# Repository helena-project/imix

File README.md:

imix
====

This open source, feature packed board is an all-in-one development kit for ultra 
low power Internet-of-Things research and prototyping. With a Cortex M4 microcontroller,
BLE/ANT and 802.15.4 radio modules, sensing, battery charging, and tons of I/O,
imix has everything you need to prototype and profile your next big IoT
breakthrough. Pair imix with the [Tock](http://github.com/helena-project/tock)
operating system to quickly develop secure embedded applications.

Features:
- Codeveloped with [Tock](http://github.com/helena-project/tock), a next-generation secure embedded operating system
- ATMEL SAM4L low power microcontroller with a Cortex M4 core
- NRF51422 radio with a Cortex M0 core for communication over Bluetooth Low Energy or ANT
- AT86RF233 radio for communication over 802.15.4
- Low power 3-axis linear accelerometer + 3-axis magnetometer
- Temperature + humidity sensor
- Digital light sensor
- Serial-to-USB and native USB ports
- Auditable True Random Number Generator
- Individually turn each subsystem completely on or off
- Easily measure the power consumption of each subsystem
- Compatible with most Arduino shields
- Integrated lithium polymer battery charger, and optional battery clips for the standard 18650 size

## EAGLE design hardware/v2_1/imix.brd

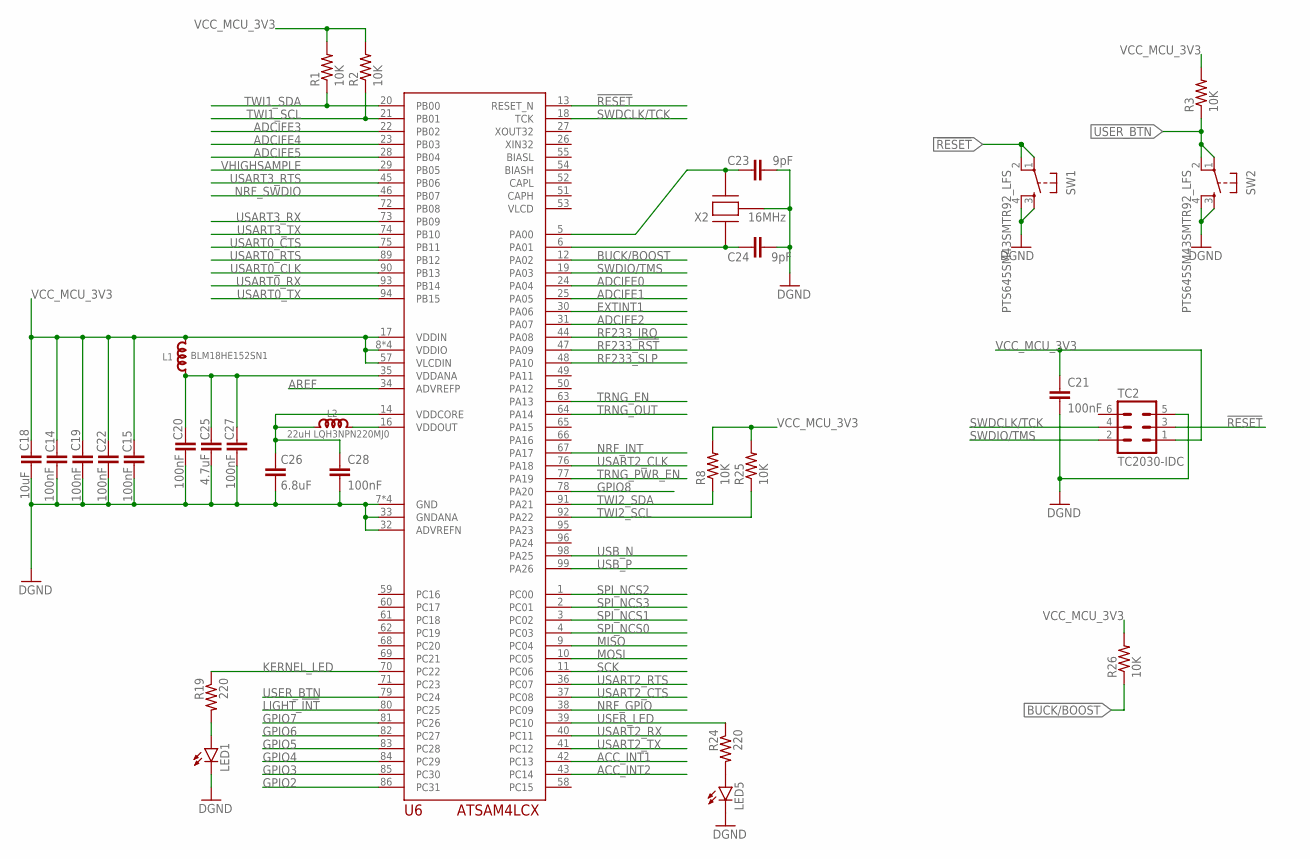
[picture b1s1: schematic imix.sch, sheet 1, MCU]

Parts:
C14, C15, C19, C20, C21, C22, C27, C28: 100nF; C0603
C18: 10uF; C0603
C23, C24: 9pF; C0603
C25: 4.7uF; C0603
C26: 6.8uF; C0603
L1: BLM18HE152SN1; L0603
L2: 22uH LQH3NPN220MJ0; L1212
LED1, LED5: LED-BLUE0603; LED-0603
R1, R2, R3, R8, R25, R26: 10K; 0603-RES
R19, R24: 220; 0603-RES
SW1, SW2: PTS645SM43SMTR92_LFS; TAC_SWITCH_6X6
TC2: TC2030-IDC
U6: ATSAM4LCX_100; TQFP100
X2: 16MHz; CTS_405_SERIES

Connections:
!RESET: SW1.1, SW1.2, TC2.3, U6.13 (RESET_N); also elsewhere on the board
ACC_INT1: U6.42 (PC13); also elsewhere on the board
ACC_INT2: U6.43 (PC14); also elsewhere on the board
ADCIFE0: U6.24 (PA04); also elsewhere on the board
ADCIFE1: U6.25 (PA05); also elsewhere on the board
ADCIFE2: U6.31 (PA07); also elsewhere on the board
ADCIFE3: U6.22 (PB02); also elsewhere on the board
ADCIFE4: U6.23 (PB03); also elsewhere on the board
ADCIFE5: U6.28 (PB04); also elsewhere on the board
AREF: U6.34 (ADVREFP); also elsewhere on the board
BIASH: U6.54 (BIASH)
BIASL: U6.55 (BIASL)
BUCK/BOOST: R26.1, U6.12 (PA02)
EXTINT1: U6.30 (PA06); also elsewhere on the board
GND: C14.1, C15.1, C18.1, C19.1, C20.2, C21.2, C22.1, C23.2, C24.2, C25.2, C26.2, C27.2, C28.2, LED1.C, LED5.C, SW1.3, SW1.4, SW2.3, SW2.4, TC2.5, U6.7 (GND), U6.15 (GND), U6.32 (ADVREFN), U6.33 (GNDANA), U6.56 (GND), U6.100 (GND), X2.CASE@2 (CASE), X2.CASE@4 (CASE); also elsewhere on the board
GPIO2: U6.86 (PC31); also elsewhere on the board
GPIO3: U6.85 (PC30); also elsewhere on the board
GPIO4: U6.84 (PC29); also elsewhere on the board
GPIO5: U6.83 (PC28); also elsewhere on the board
GPIO6: U6.82 (PC27); also elsewhere on the board
GPIO7: U6.81 (PC26); also elsewhere on the board
GPIO8: U6.78 (PA20); also elsewhere on the board
KERNEL_LED: R19.1, U6.70 (PC22)
LIGHT_!INT: U6.80 (PC25); also elsewhere on the board
MCU_VOUT3.3: L2.2, U6.16 (VDDOUT)
MISO: U6.9 (PC04); also elsewhere on the board
MOSI: U6.10 (PC05); also elsewhere on the board
unnamed: C20.1, C25.1, C27.1, L1.1, U6.35 (VDDANA)
unnamed: C24.1, U6.6 (PA01), X2.1
unnamed: C26.1, C28.1, L2.1, U6.14 (VDDCORE)
unnamed: C23.1, U6.5 (PA00), X2.3 (2)
unnamed: LED1.A, R19.2
unnamed: LED5.A, R24.2
NRF_GPIO: U6.38 (PC09); also elsewhere on the board
NRF_INT: U6.67 (PA17); also elsewhere on the board
NRF_SWDIO: U6.46 (PB07); also elsewhere on the board
RF233_!RST: U6.47 (PA09); also elsewhere on the board
RF233_IRQ: U6.44 (PA08); also elsewhere on the board
RF233_SLP: U6.48 (PA10); also elsewhere on the board
SCK: U6.11 (PC06); also elsewhere on the board
SPI_NCS0: U6.4 (PC03); also elsewhere on the board
SPI_NCS1: U6.3 (PC02); also elsewhere on the board
SPI_NCS2: U6.1 (PC00); also elsewhere on the board
SPI_NCS3: U6.2 (PC01); also elsewhere on the board
SWDCLK/TCK: TC2.4, U6.18 (TCK)
SWDIO/TMS: TC2.2, U6.19 (PA03)
TRNG_EN: U6.63 (PA13); also elsewhere on the board
TRNG_OUT: U6.64 (PA14); also elsewhere on the board
TRNG_PWR_EN: U6.77 (PA19); also elsewhere on the board
TWI1_SCL: R2.1, U6.21 (PB01); also elsewhere on the board
TWI1_SDA: R1.1, U6.20 (PB00); also elsewhere on the board
TWI2_SCL: R25.1, U6.92 (PA22); also elsewhere on the board
TWI2_SDA: R8.1, U6.91 (PA21); also elsewhere on the board
USART0_CLK: U6.90 (PB13); also elsewhere on the board
USART0_CTS: U6.75 (PB11); also elsewhere on the board
USART0_RTS: U6.89 (PB12); also elsewhere on the board
USART0_RX: U6.93 (PB14); also elsewhere on the board
USART0_TX: U6.94 (PB15); also elsewhere on the board
USART2_CLK: U6.76 (PA18); also elsewhere on the board
USART2_CTS: U6.37 (PC08); also elsewhere on the board
USART2_RTS: U6.36 (PC07); also elsewhere on the board
USART2_RX: U6.40 (PC11); also elsewhere on the board
USART2_TX: U6.41 (PC12); also elsewhere on the board
USART3_RTS: U6.45 (PB06); also elsewhere on the board
USART3_RX: U6.73 (PB09); also elsewhere on the board
USART3_TX: U6.74 (PB10); also elsewhere on the board
USB_N: U6.98 (PA25); also elsewhere on the board
USB_P: U6.99 (PA26); also elsewhere on the board
USER_BTN: R3.1, SW2.1, SW2.2, U6.79 (PC24); also elsewhere on the board
USER_LED: R24.1, U6.39 (PC10)
VCC_MCU_3V3: C14.2, C15.2, C18.2, C19.2, C21.1, C22.2, L1.2, R1.2, R2.2, R3.2, R8.2, R25.2, R26.2, TC2.1, U6.8 (VDDIO), U6.17 (VDDIN), U6.57 (VLCDIN), U6.87 (VDDIO), U6.88 (VDDIO), U6.97 (VDDIO); also elsewhere on the board
VHIGHSAMPLE: U6.29 (PB05); also elsewhere on the board

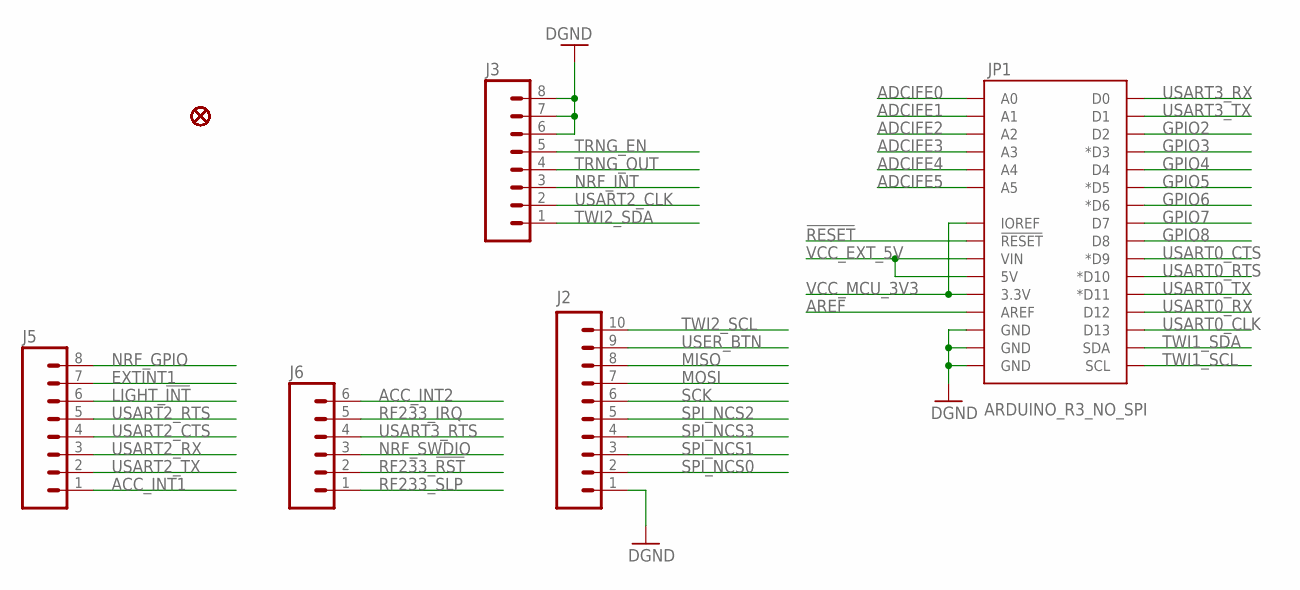
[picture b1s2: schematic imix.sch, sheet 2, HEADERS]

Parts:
J2: M10NO_SILK_PTH_FEMALE; 1X10_NO_SILK
J3, J5: M08NO_SILK_FEMALE_PTH; 1X08_NO_SILK
J6: M06NO_SILK_FEMALE_PTH; 1X06_NO_SILK
JP1: ARDUINO_R3_NO_SPI; ARDUINO_R3_NO_HOLES_NO_SPI
U$2, U$3, U$5, U$6, U$7, U$8, U$10, U$11, U$12, U$13, U$14, U$15, U$16, U$17, U$18: FIDUCIAL

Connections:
!RESET: JP1.RESET@1 (!RESET!); also elsewhere on the board
ACC_INT1: J5.1; also elsewhere on the board
ACC_INT2: J6.6; also elsewhere on the board
ADCIFE0: JP1.A0; also elsewhere on the board
ADCIFE1: JP1.A1; also elsewhere on the board
ADCIFE2: JP1.A2; also elsewhere on the board
ADCIFE3: JP1.A3; also elsewhere on the board
ADCIFE4: JP1.A4; also elsewhere on the board
ADCIFE5: JP1.A5; also elsewhere on the board
AREF: JP1.AREF; also elsewhere on the board
EXTINT1: J5.7; also elsewhere on the board
GND: J2.1, J3.6, J3.7, J3.8, JP1.GND@1 (GND), JP1.GND@2 (GND), JP1.GND@3 (GND); also elsewhere on the board
GPIO2: JP1.D2; also elsewhere on the board
GPIO3: JP1.D3 (*D3); also elsewhere on the board
GPIO4: JP1.D4; also elsewhere on the board
GPIO5: JP1.D5 (*D5); also elsewhere on the board
GPIO6: JP1.D6 (*D6); also elsewhere on the board
GPIO7: JP1.D7; also elsewhere on the board
GPIO8: JP1.D8; also elsewhere on the board
LIGHT_!INT: J5.6; also elsewhere on the board
MISO: J2.8; also elsewhere on the board
MOSI: J2.7; also elsewhere on the board
NRF_GPIO: J5.8; also elsewhere on the board
NRF_INT: J3.3; also elsewhere on the board
NRF_SWDIO: J6.3; also elsewhere on the board
RF233_!RST: J6.2; also elsewhere on the board
RF233_IRQ: J6.5; also elsewhere on the board
RF233_SLP: J6.1; also elsewhere on the board
SCK: J2.6; also elsewhere on the board
SPI_NCS0: J2.2; also elsewhere on the board
SPI_NCS1: J2.3; also elsewhere on the board
SPI_NCS2: J2.5; also elsewhere on the board
SPI_NCS3: J2.4; also elsewhere on the board
TRNG_EN: J3.5; also elsewhere on the board
TRNG_OUT: J3.4; also elsewhere on the board
TWI1_SCL: JP1.SCL; also elsewhere on the board
TWI1_SDA: JP1.SDA; also elsewhere on the board
TWI2_SCL: J2.10; also elsewhere on the board
TWI2_SDA: J3.1; also elsewhere on the board
USART0_CLK: JP1.D13; also elsewhere on the board
USART0_CTS: JP1.D9 (*D9); also elsewhere on the board
USART0_RTS: JP1.D10 (*D10); also elsewhere on the board
USART0_RX: JP1.D12; also elsewhere on the board
USART0_TX: JP1.D11 (*D11); also elsewhere on the board
USART2_CLK: J3.2; also elsewhere on the board
USART2_CTS: J5.4; also elsewhere on the board
USART2_RTS: J5.5; also elsewhere on the board
USART2_RX: J5.3; also elsewhere on the board
USART2_TX: J5.2; also elsewhere on the board
USART3_RTS: J6.4; also elsewhere on the board
USART3_RX: JP1.D0; also elsewhere on the board
USART3_TX: JP1.D1; also elsewhere on the board
USER_BTN: J2.9; also elsewhere on the board
VCC_EXT_5V: JP1.5V, JP1.VIN; also elsewhere on the board
VCC_MCU_3V3: JP1.3.3V, JP1.IOREF; also elsewhere on the board

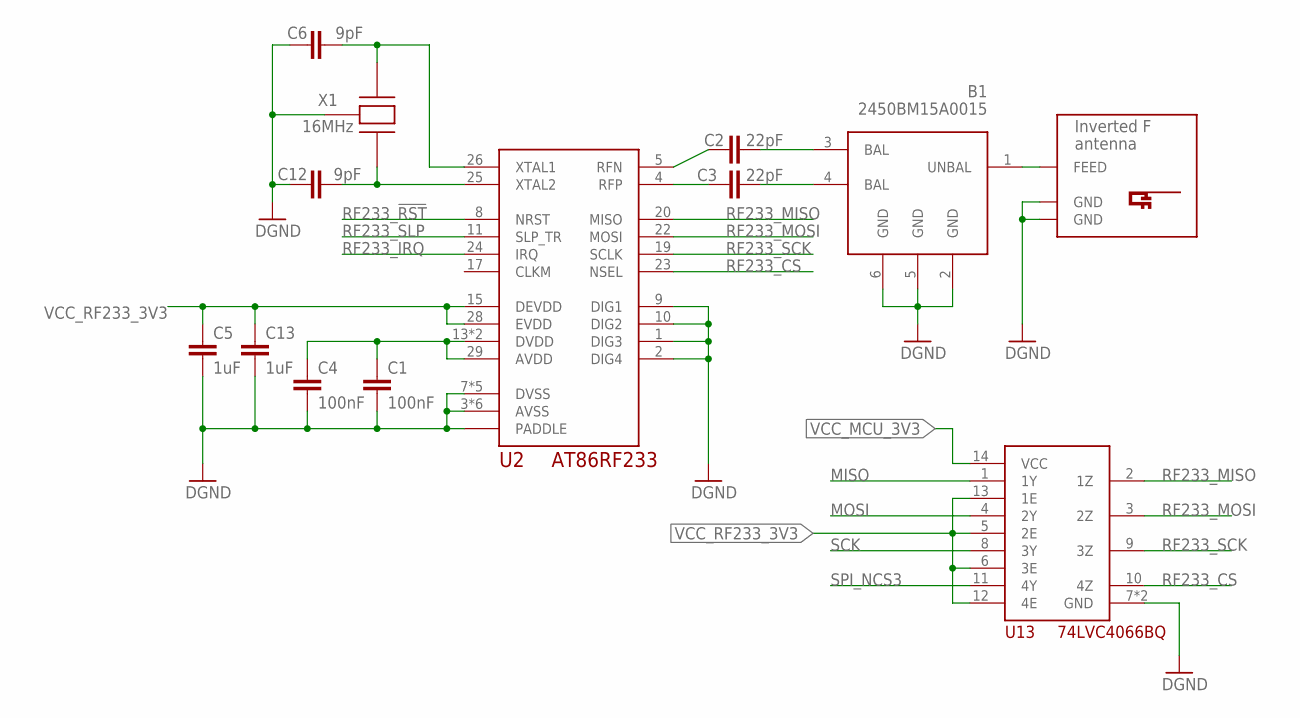
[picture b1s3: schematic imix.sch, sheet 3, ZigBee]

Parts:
B1: 2450BM15A0015; BALUN0805
C1, C4: 100nF; C0603
C2, C3: 22pF; C0603
C5, C13: 1uF; C0603
C6, C12: 9pF; C0603
U2: AT86RF233; 32QN2
U13: 74LVC4066BQ; DHVQFN14
U$1: INVERTED_F_ANTENNA-2; DN007-2
X1: 16MHz; CTS_405_SERIES

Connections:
GND: B1.2 (GND), B1.5 (GND), B1.6 (GND), C1.2, C4.2, C5.2, C6.1, C12.1, C13.2, U2.1 (DIG3), U2.2 (DIG4), U2.3 (AVSS), U2.6 (AVSS), U2.7 (DVSS), U2.9 (DIG1), U2.10 (DIG2), U2.12 (DVSS), U2.16 (DVSS), U2.18 (DVSS), U2.21 (DVSS), U2.27 (AVSS), U2.30 (AVSS), U2.31 (AVSS), U2.32 (AVSS), U2.PADDLE, U13.7 (GND), U13.PADDLE (GND), U$1.GND, U$1.GND@1 (GND), X1.CASE@2 (CASE), X1.CASE@4 (CASE); also elsewhere on the board
MISO: U13.1 (1Y); also elsewhere on the board
MOSI: U13.4 (2Y); also elsewhere on the board
unnamed: C2.2, U2.5 (RFN)
unnamed: C1.1, C4.1, U2.13 (DVDD), U2.14 (DVDD), U2.29 (AVDD)
unnamed: C6.2, U2.26 (XTAL1), X1.1
unnamed: C3.2, U2.4 (RFP)
unnamed: B1.3 (BAL), C2.1
unnamed: C12.2, U2.25 (XTAL2), X1.3 (2)
unnamed: B1.4 (BAL), C3.1
unnamed: B1.1 (UNBAL), U$1.FEED
RF233_!RST: U2.8 (NRST); also elsewhere on the board
RF233_CS: U2.23 (NSEL), U13.10 (4Z)
RF233_IRQ: U2.24 (IRQ); also elsewhere on the board
RF233_MISO: U2.20 (MISO), U13.2 (1Z)
RF233_MOSI: U2.22 (MOSI), U13.3 (2Z)
RF233_SCK: U2.19 (SCLK), U13.9 (3Z)
RF233_SLP: U2.11 (SLP_TR); also elsewhere on the board
SCK: U13.8 (3Y); also elsewhere on the board
SPI_NCS3: U13.11 (4Y); also elsewhere on the board
VCC_MCU_3V3: U13.14 (VCC); also elsewhere on the board
VCC_RF233_3V3: C5.1, C13.1, U2.15 (DEVDD), U2.28 (EVDD), U13.5 (2E), U13.6 (3E), U13.12 (4E), U13.13 (1E); also elsewhere on the board

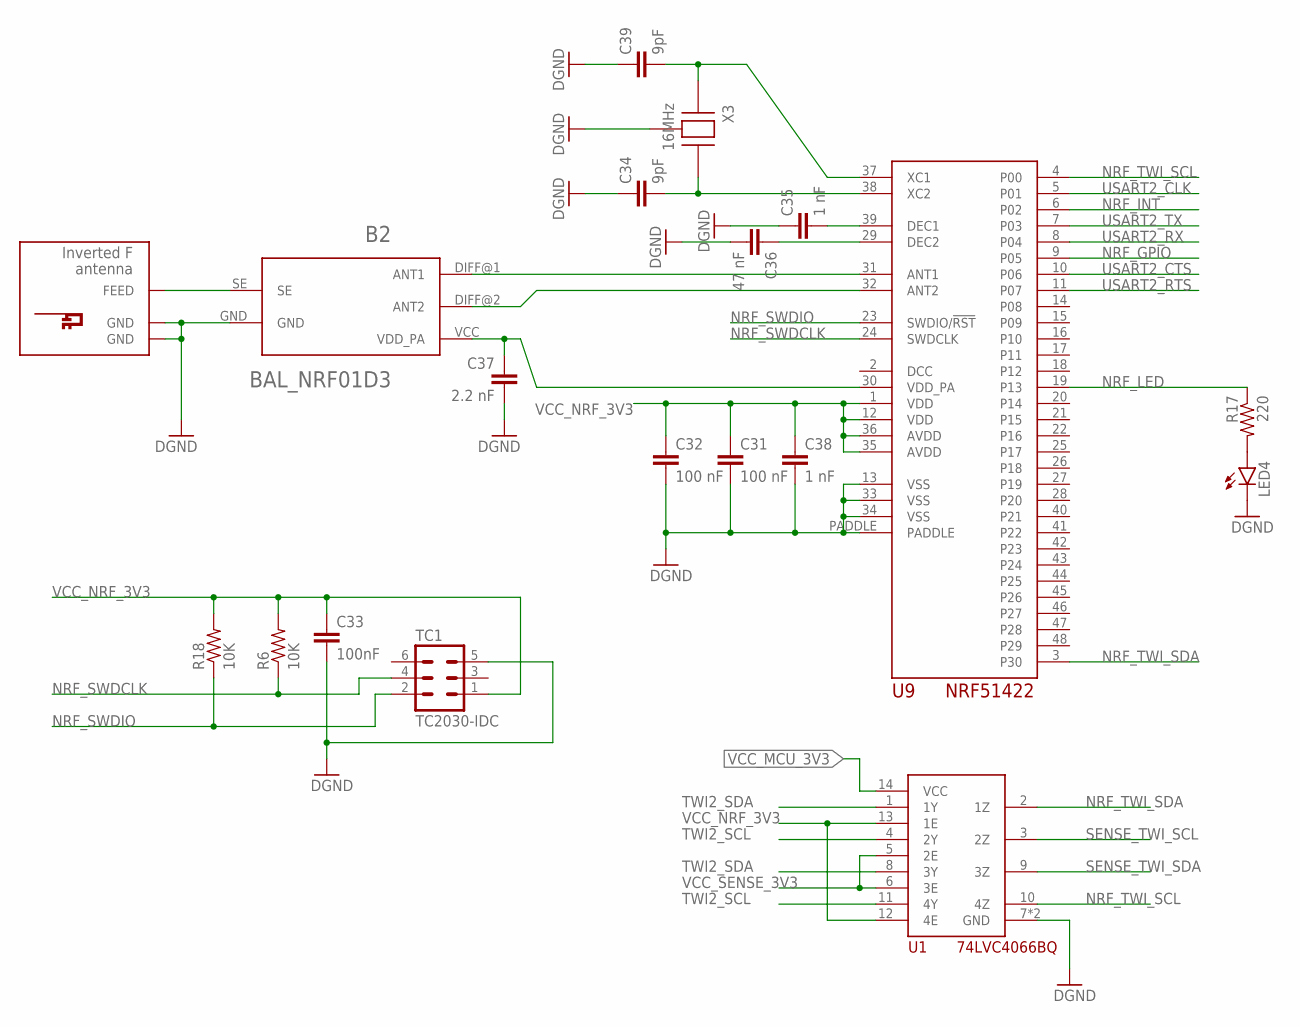
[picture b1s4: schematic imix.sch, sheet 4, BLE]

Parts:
B2: BAL_NRF01D3
C31, C32: 100 nF; C0603
C33: 100nF; C0603
C34, C39: 9pF; C0603
C35, C38: 1 nF; C0603
C36: 47 nF; C0603
C37: 2.2 nF; C0603
LED4: LED-BLUE0603; LED-0603
R6, R18: 10K; 0603-RES
R17: 220; 0603-RES
TC1: TC2030-IDC
U1: 74LVC4066BQ; DHVQFN14
U9: NRF51422; QFN48_6X6
U$4: INVERTED_F_ANTENNA-2; DN007-2
X3: 16MHz; CTS_405_SERIES

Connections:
GND: B2.GND, C31.2, C32.2, C33.2, C34.1, C35.1, C36.2, C37.2, C38.2, C39.1, LED4.C, TC1.5, U1.7 (GND), U1.PADDLE (GND), U9.13 (VSS), U9.33 (VSS), U9.34 (VSS), U9.PADDLE, U$4.GND, U$4.GND@1 (GND), X3.CASE@2 (CASE), X3.CASE@4 (CASE); also elsewhere on the board
unnamed: B2.SE, U$4.FEED
unnamed: B2.VCC (VDD_PA), C37.1, U9.30 (VDD_PA)
unnamed: C34.2, U9.38 (XC2), X3.3 (2)
unnamed: C39.2, U9.37 (XC1), X3.1
unnamed: C35.2, U9.39 (DEC1)
unnamed: C36.1, U9.29 (DEC2)
unnamed: B2.DIFF@1 (ANT1), U9.31 (ANT1)
unnamed: B2.DIFF@2 (ANT2), U9.32 (ANT2)
unnamed: LED4.A, R17.2
NRF_GPIO: U9.9 (P05); also elsewhere on the board
NRF_INT: U9.6 (P02); also elsewhere on the board
NRF_LED: R17.1, U9.19 (P13)
NRF_SWDCLK: R6.1, TC1.4, U9.24 (SWDCLK)
NRF_SWDIO: R18.1, TC1.2, U9.23 (SWDIO/!RST); also elsewhere on the board
NRF_TWI_SCL: U1.10 (4Z), U9.4 (P00)
NRF_TWI_SDA: U1.2 (1Z), U9.3 (P30)
SENSE_TWI_SCL: U1.3 (2Z); also elsewhere on the board
SENSE_TWI_SDA: U1.9 (3Z); also elsewhere on the board
TWI2_SCL: U1.4 (2Y), U1.11 (4Y); also elsewhere on the board
TWI2_SDA: U1.1 (1Y), U1.8 (3Y); also elsewhere on the board
USART2_CLK: U9.5 (P01); also elsewhere on the board
USART2_CTS: U9.10 (P06); also elsewhere on the board
USART2_RTS: U9.11 (P07); also elsewhere on the board
USART2_RX: U9.8 (P04); also elsewhere on the board
USART2_TX: U9.7 (P03); also elsewhere on the board
VCC_MCU_3V3: U1.14 (VCC); also elsewhere on the board
VCC_NRF_3V3: C31.1, C32.1, C33.1, C38.1, R6.2, R18.2, TC1.1, U1.12 (4E), U1.13 (1E), U9.1 (VDD), U9.12 (VDD), U9.35 (AVDD), U9.36 (AVDD); also elsewhere on the board
VCC_SENSE_3V3: U1.5 (2E), U1.6 (3E); also elsewhere on the board

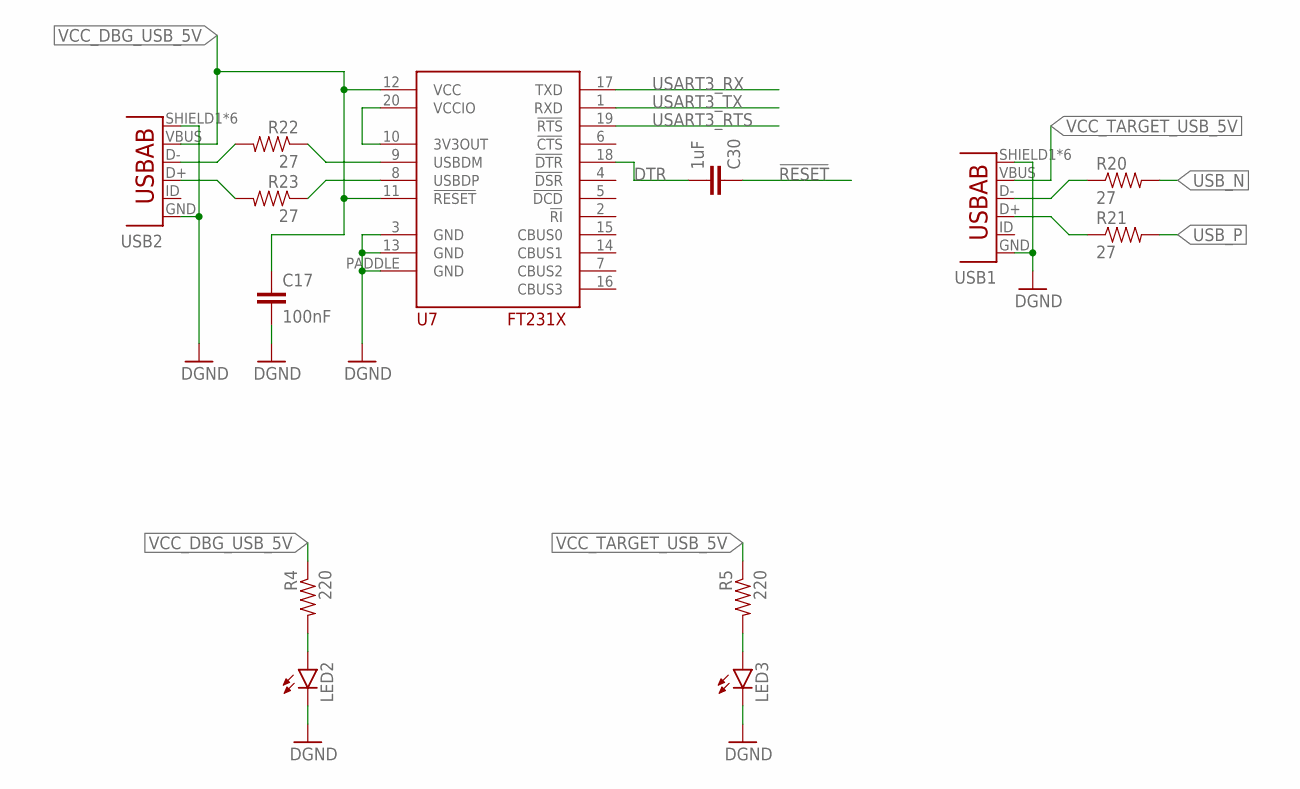
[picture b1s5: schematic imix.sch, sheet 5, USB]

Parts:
C17: 100nF; C0603
C30: 1uF; C0603
LED2, LED3: LED-BLUE0603; LED-0603
R4, R5: 220; 0603-RES
R20, R21, R22, R23: 27; 0603-RES
U7: FT231X; QFN20
USB1, USB2: USB-AB; USB-AB-MICRO-SMD

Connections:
!RESET: C30.1; also elsewhere on the board
DTR: C30.2, U7.18 (!DTR)
GND: C17.2, LED2.C, LED3.C, U7.3 (GND), U7.13 (GND), U7.PADDLE (GND), USB1.GND, USB1.SHIELD1 (SHIELD), USB1.SHIELD2 (SHIELD), USB1.SHIELD3 (SHIELD), USB1.SHIELD4 (SHIELD), USB1.SHIELD5 (SHIELD), USB1.SHIELD6 (SHIELD), USB2.GND, USB2.SHIELD1 (SHIELD), USB2.SHIELD2 (SHIELD), USB2.SHIELD3 (SHIELD), USB2.SHIELD4 (SHIELD), USB2.SHIELD5 (SHIELD), USB2.SHIELD6 (SHIELD); also elsewhere on the board
unnamed: R20.1, USB1.D-
unnamed: U7.10 (3V3OUT), U7.20 (VCCIO)
unnamed: LED2.A, R4.2
unnamed: LED3.A, R5.2
unnamed: R22.2, USB2.D-
unnamed: R22.1, U7.9 (USBDM)
unnamed: R23.2, USB2.D+
unnamed: R23.1, U7.8 (USBDP)
unnamed: R21.1, USB1.D+
USART3_RTS: U7.19 (!RTS); also elsewhere on the board
USART3_RX: U7.17 (TXD); also elsewhere on the board
USART3_TX: U7.1 (RXD); also elsewhere on the board
USB_N: R20.2; also elsewhere on the board
USB_P: R21.2; also elsewhere on the board
VCC_DBG_USB_5V: C17.1, R4.1, U7.11 (!RESET), U7.12 (VCC), USB2.VBUS; also elsewhere on the board
VCC_TARGET_USB_5V: R5.1, USB1.VBUS; also elsewhere on the board

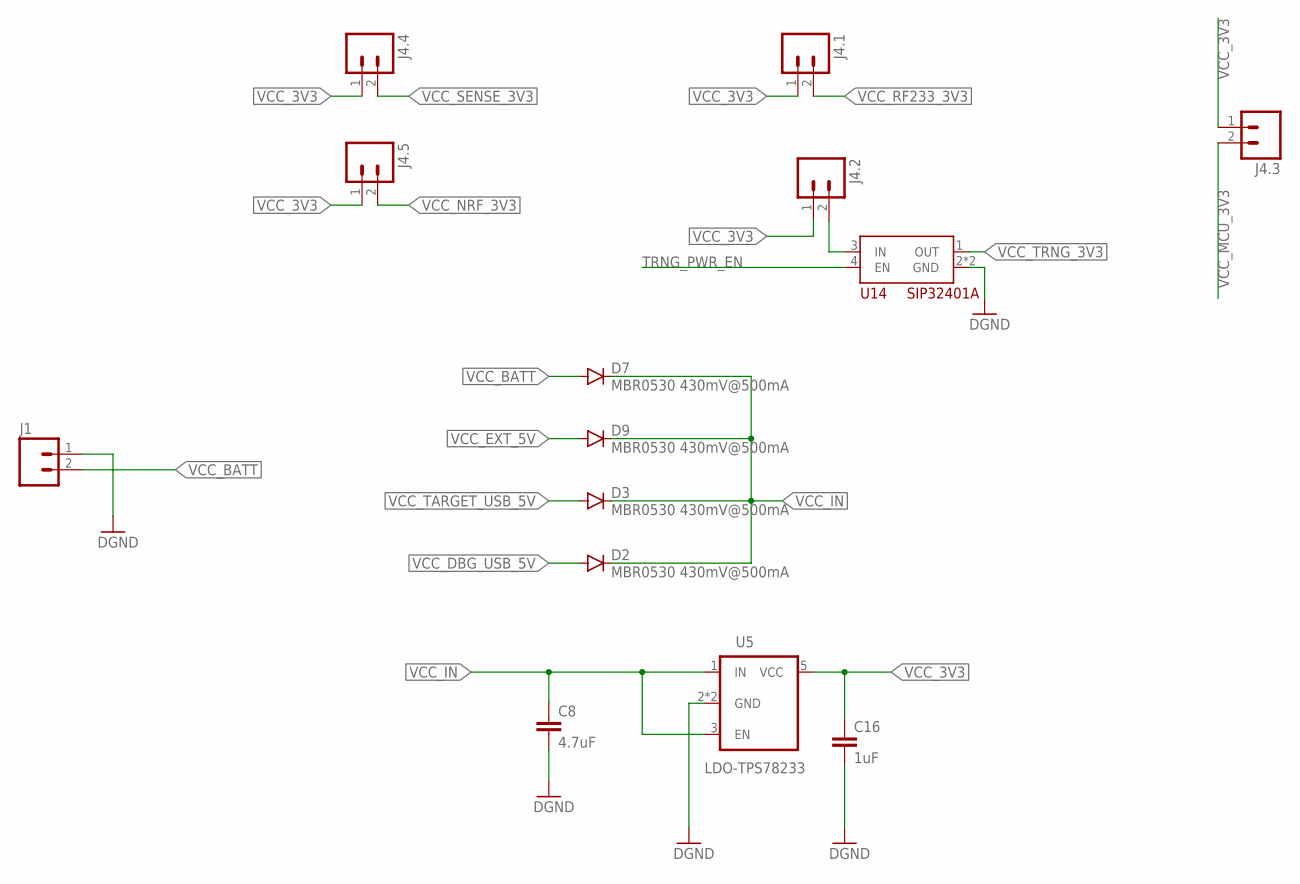
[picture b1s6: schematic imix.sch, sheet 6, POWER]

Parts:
C8: 4.7uF; C0603
C16: 1uF; C0603
D2, D3, D7, D9: MBR0530 430mV@500mA; SOD-123
J1: M02-JST-2MM-SMT; JST-2-SMD
J4.1, J4.2, J4.3, J4.4, J4.5: M021X02_NO_SILK; 1X02_NO_SILK
U5: LDO-TPS78233; SOT23-5
U14: SIP32401A; TDFN4

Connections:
GND: C8.2, C16.2, J1.1 (2), U5.2 (GND), U5.4 (GND), U14.2 (GND), U14.PADDLE (GND); also elsewhere on the board
unnamed: J4.2.2, U14.3 (IN)
TRNG_PWR_EN: U14.4 (EN); also elsewhere on the board
VCC_3V3: C16.1, J4.1.1, J4.2.1, J4.3.1, J4.4.1, J4.5.1, U5.5 (VCC)
VCC_BATT: D7.A, J1.2 (1)
VCC_DBG_USB_5V: D2.A; also elsewhere on the board
VCC_EXT_5V: D9.A; also elsewhere on the board
VCC_IN: C8.1, D2.C, D3.C, D7.C, D9.C, U5.1 (IN), U5.3 (EN)
VCC_MCU_3V3: J4.3.2; also elsewhere on the board
VCC_NRF_3V3: J4.5.2; also elsewhere on the board
VCC_RF233_3V3: J4.1.2; also elsewhere on the board
VCC_SENSE_3V3: J4.4.2; also elsewhere on the board
VCC_TARGET_USB_5V: D3.A; also elsewhere on the board
VCC_TRNG_3V3: U14.1 (OUT); also elsewhere on the board

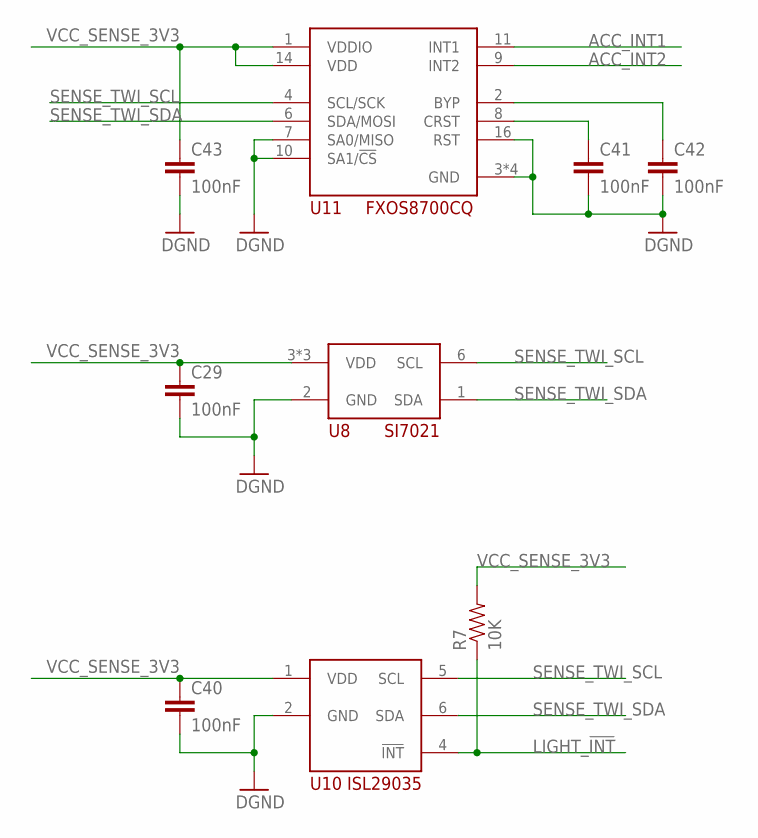
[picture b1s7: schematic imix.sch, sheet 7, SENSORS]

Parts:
C29, C40, C41, C42, C43: 100nF; C0603
R7: 10K; 0603-RES
U8: SI7021
U10: ISL29035
U11: FX0S8700CQ; QFN16_3,5

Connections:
ACC_INT1: U11.11 (INT1); also elsewhere on the board
ACC_INT2: U11.9 (INT2); also elsewhere on the board
GND: C29.2, C40.2, C41.2, C42.2, C43.2, U8.2 (GND), U10.2 (GND), U11.3 (GND), U11.5 (GND), U11.7 (SA0/MISO), U11.10 (SA1/!CS), U11.12 (GND), U11.13 (GND), U11.16 (RST); also elsewhere on the board
LIGHT_!INT: R7.1, U10.4 (!INT); also elsewhere on the board
unnamed: C41.1, U11.8 (CRST)
unnamed: C42.1, U11.2 (BYP)
SENSE_TWI_SCL: U8.6 (SCL), U10.5 (SCL), U11.4 (SCL/SCK); also elsewhere on the board
SENSE_TWI_SDA: U8.1 (SDA), U10.6 (SDA), U11.6 (SDA/MOSI); also elsewhere on the board
VCC_SENSE_3V3: C29.1, C40.1, C43.1, R7.2, U8.3 (VDD), U8.4 (VDD), U8.5 (VDD), U10.1 (VDD), U11.1 (VDDIO), U11.14 (VDD); also elsewhere on the board

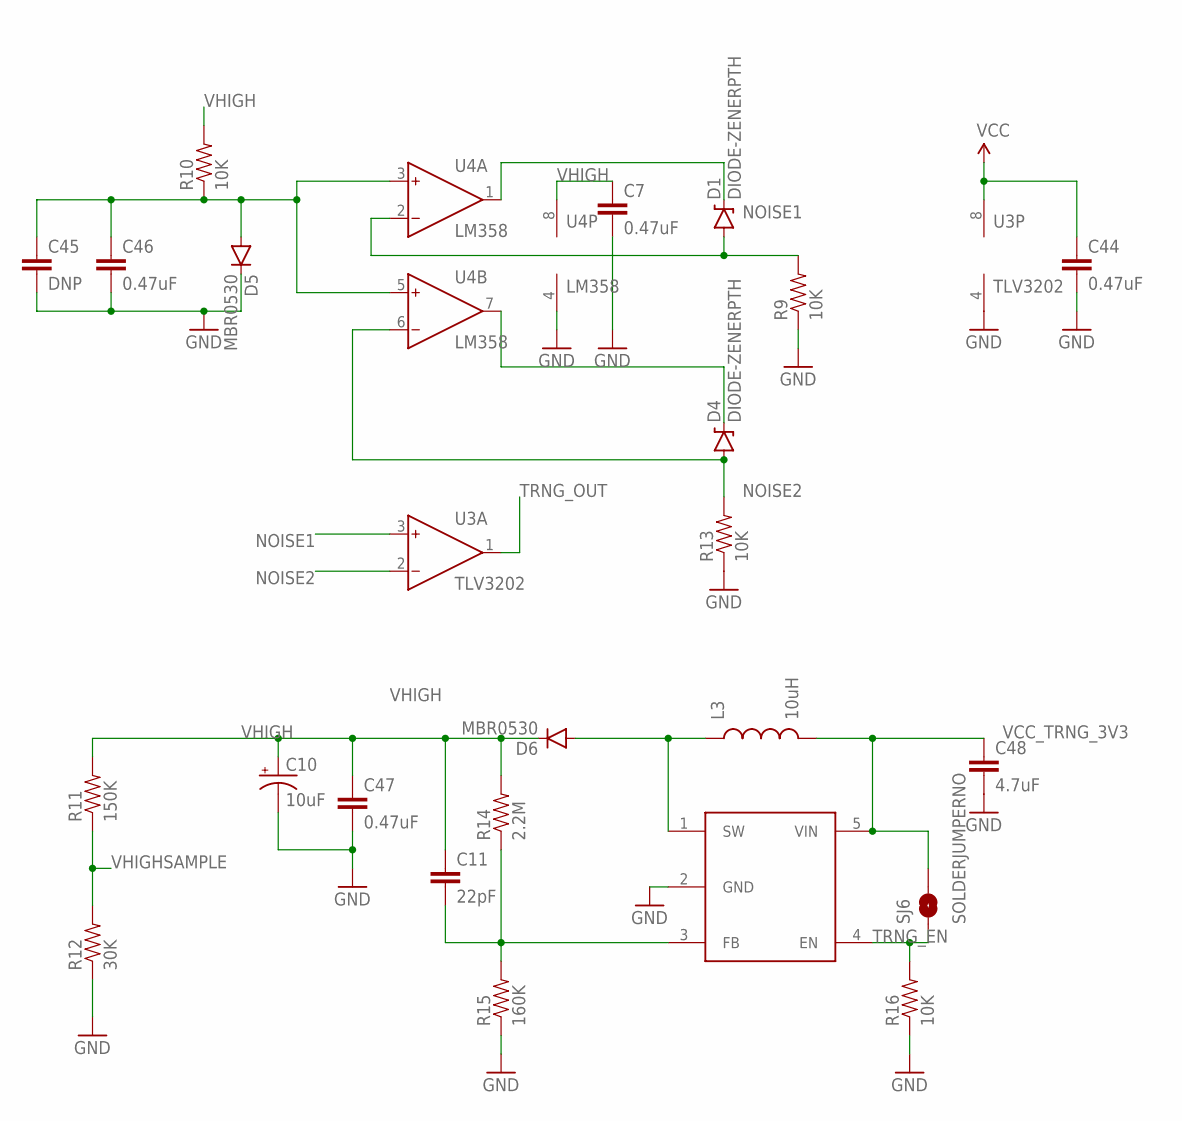
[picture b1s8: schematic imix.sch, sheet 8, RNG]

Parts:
C7, C44, C46: 0.47uF; C0603
C10: 10uF; PANASONIC_C
C11: 22pF; C0603
C45: DNP; C0603
C47: 0.47uF; C0603-NOSILK
C48: 4.7uF; C0603-NOSILK
D1, D4: DIODE-ZENERPTH; DIODE-ZENER; MPN 610-1N759A
D5, D6: MBR0530; SOD-123
L3: 10uH; 0805
R9, R10, R13, R16: 10K; 0603-RES
R11: 150K; 0603-RES
R12: 30K; 0603-RES
R14: 2.2M; 0603-RES
R15: 160K; 0603-RES
SJ6: SOLDERJUMPERNO; SJ_2S-NO
U3: TLV3202; SO8
U4: LM358; SO8
U12: 296-12686-1-ND; SOT23-5

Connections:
GND: C7.2, C10.-, C44.2, C45.2, C46.2, C47.2, C48.2, D5.C, R9.1, R12.1, R13.1, R15.1, R16.1, U3.4 (V-), U4.4 (V-), U12.2 (GND); also elsewhere on the board
unnamed: D6.A, L3.1, U12.1 (SW)
unnamed: C11.2, R14.1, R15.2, U12.3 (FB)
unnamed: D1.P$1 (C), U4.1 (OUT)
unnamed: D4.P$1 (C), U4.7 (OUT)
unnamed: C45.1, C46.1, D5.A, R10.1, U4.3 (IN+), U4.5 (IN+)
NOISE1: D1.P$2 (A), R9.2, U3.3 (IN+), U4.2 (IN-)
NOISE2: D4.P$2 (A), R13.2, U3.2 (IN-), U4.6 (IN-)
TRNG_EN: R16.2, SJ6.1, U12.4 (EN); also elsewhere on the board
TRNG_OUT: U3.1 (OUT); also elsewhere on the board
VCC_TRNG_3V3: C44.1, C48.1, L3.2, SJ6.2, U3.8 (V+), U12.5 (VIN); also elsewhere on the board
VHIGH: C7.1, C10.+, C11.1, C47.1, D6.C, R10.2, R11.2, R14.2, U4.8 (V+)
VHIGHSAMPLE: R11.1, R12.2; also elsewhere on the board

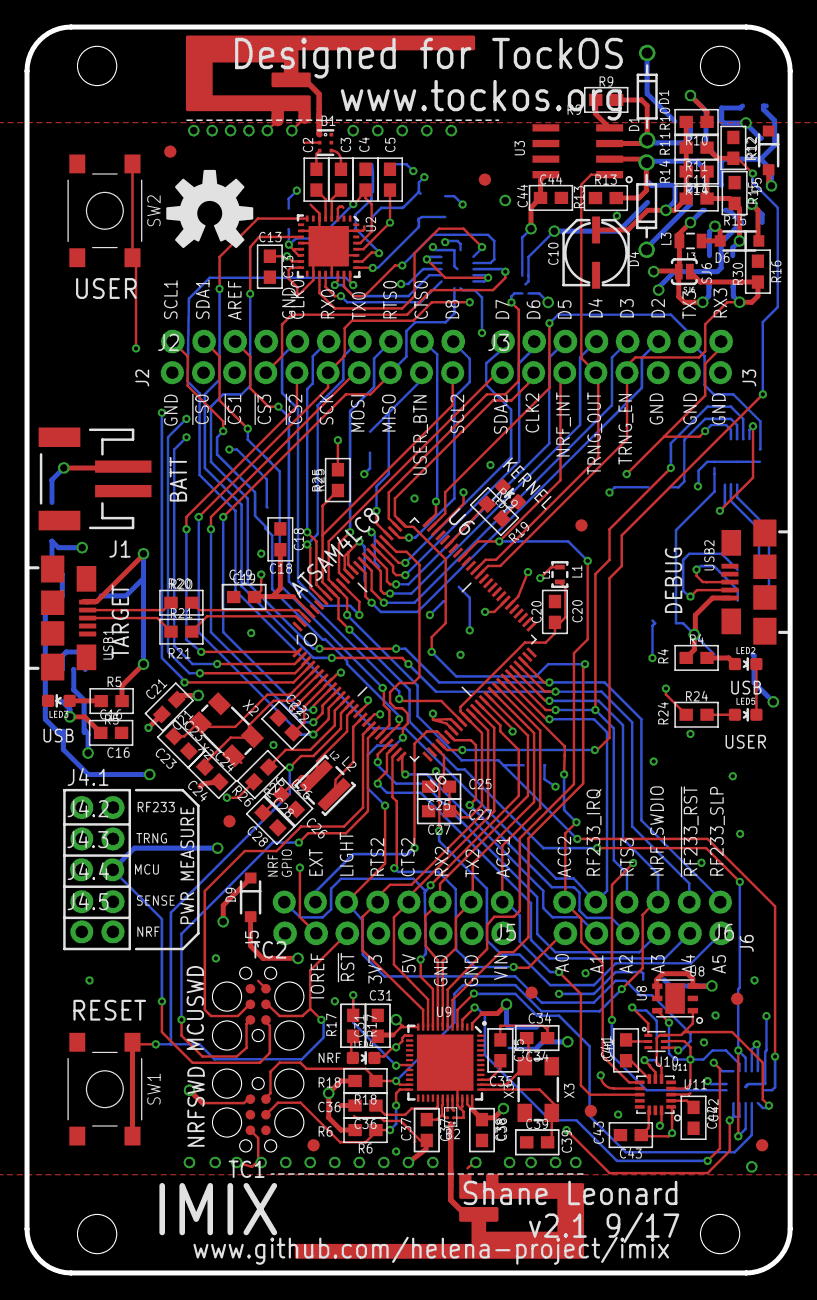
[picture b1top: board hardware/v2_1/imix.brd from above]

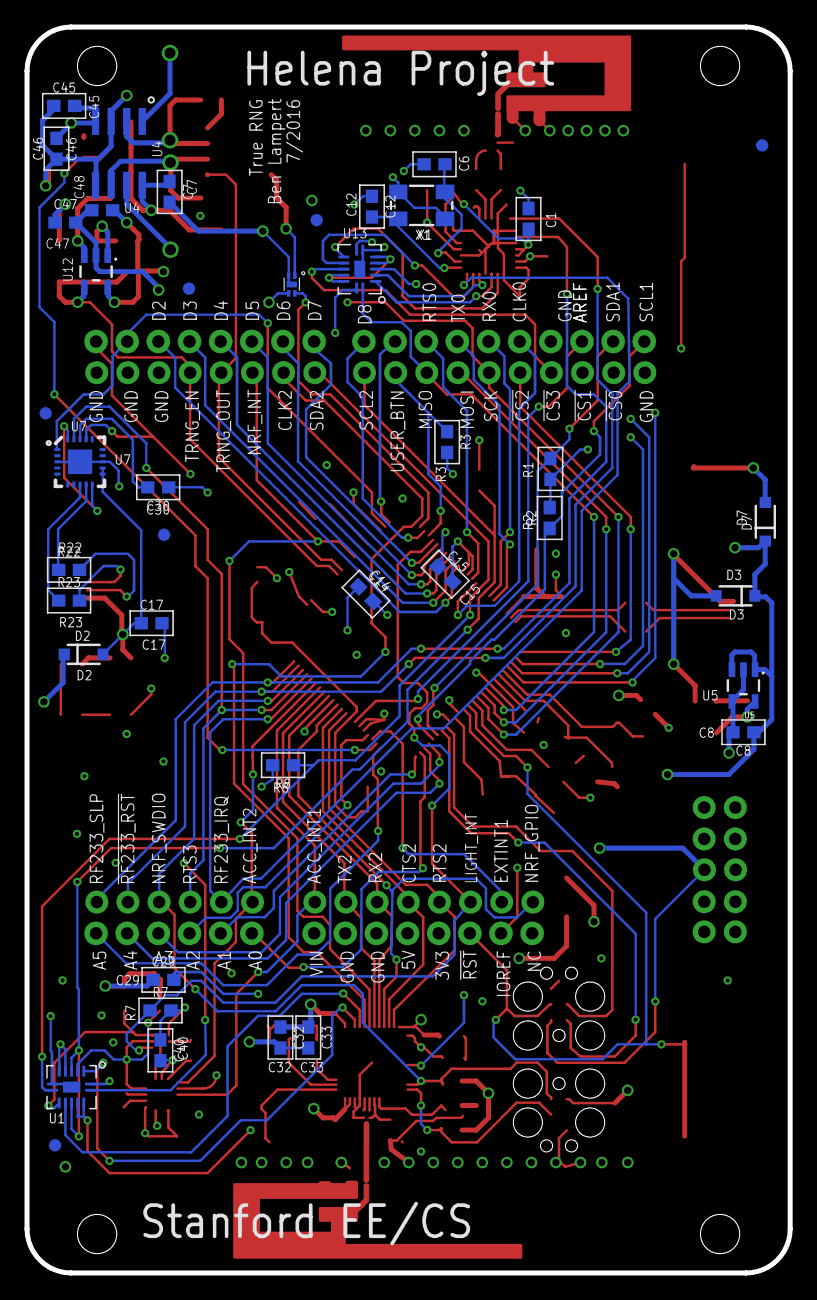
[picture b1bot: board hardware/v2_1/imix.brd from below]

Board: 4 copper layers, 62.2 x 101.6 mm, 144 parts (41 on the bottom side), 128 nets.

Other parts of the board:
U$9: OSHW-LOGO-L

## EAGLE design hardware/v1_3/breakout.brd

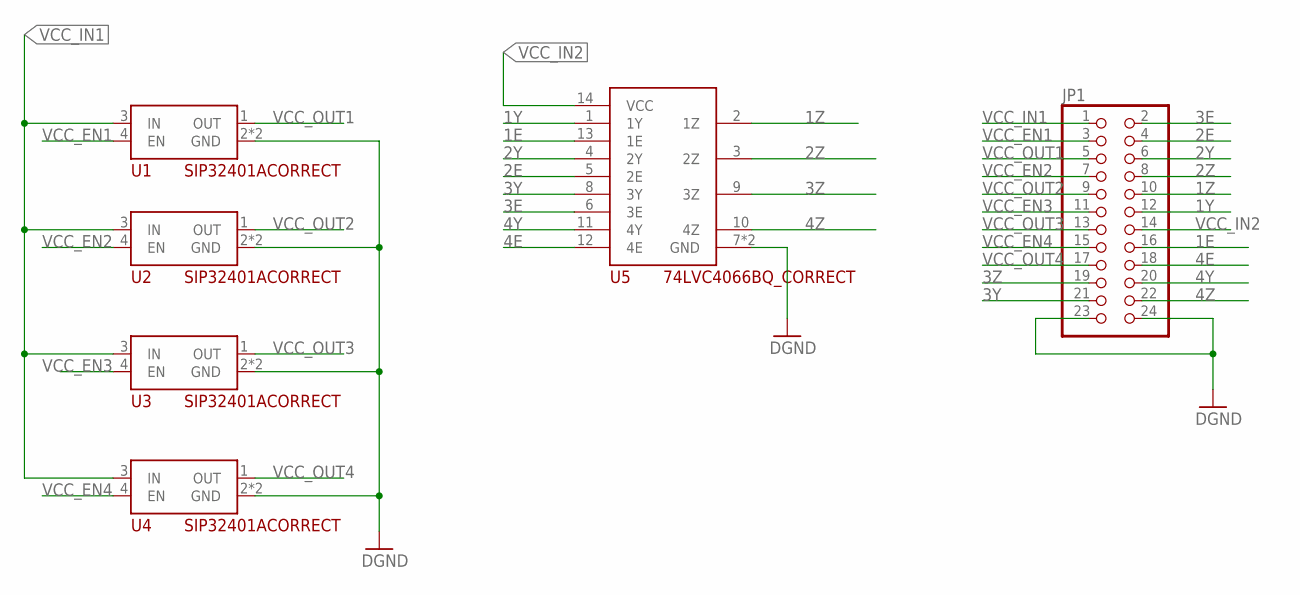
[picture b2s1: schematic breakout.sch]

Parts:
JP1: PINHD-2X12/90; 2X12/90
U1, U2, U3, U4: SIP32401ACORRECT; TDFN4_CORRECT
U5: 74LVC4066BQ_CORRECT; DHVQFN14_CORRECTED

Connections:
1E: JP1.16, U5.13 (1E)
1Y: JP1.12, U5.1 (1Y)
1Z: JP1.10, U5.2 (1Z)
2E: JP1.4, U5.5 (2E)
2Y: JP1.6, U5.4 (2Y)
2Z: JP1.8, U5.3 (2Z)
3E: JP1.2, U5.6 (3E)
3Y: JP1.21, U5.8 (3Y)
3Z: JP1.19, U5.9 (3Z)
4E: JP1.18, U5.12 (4E)
4Y: JP1.20, U5.11 (4Y)
4Z: JP1.22, U5.10 (4Z)
GND: JP1.23, JP1.24, U1.2 (GND), U1.PADDLE (GND), U2.2 (GND), U2.PADDLE (GND), U3.2 (GND), U3.PADDLE (GND), U4.2 (GND), U4.PADDLE (GND), U5.7 (GND), U5.PADDLE (GND)
VCC_EN1: JP1.3, U1.4 (EN)
VCC_EN2: JP1.7, U2.4 (EN)
VCC_EN3: JP1.11, U3.4 (EN)
VCC_EN4: JP1.15, U4.4 (EN)
VCC_IN1: JP1.1, U1.3 (IN), U2.3 (IN), U3.3 (IN), U4.3 (IN)
VCC_IN2: JP1.14, U5.14 (VCC)
VCC_OUT1: JP1.5, U1.1 (OUT)
VCC_OUT2: JP1.9, U2.1 (OUT)
VCC_OUT3: JP1.13, U3.1 (OUT)
VCC_OUT4: JP1.17, U4.1 (OUT)

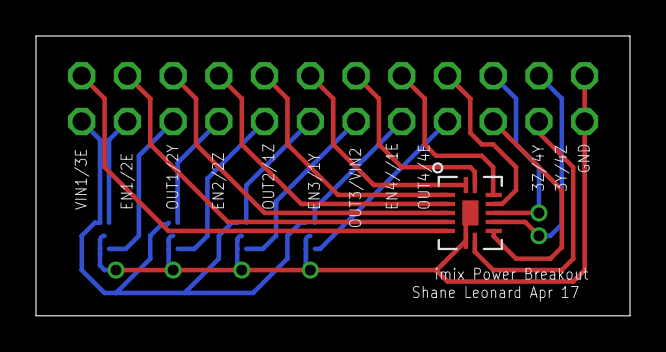
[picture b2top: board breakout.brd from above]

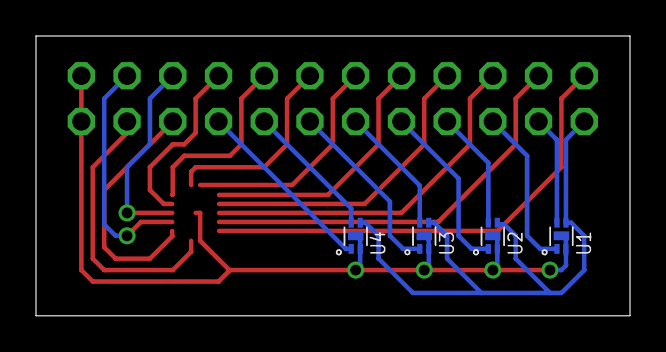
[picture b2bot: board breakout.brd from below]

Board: 2 copper layers, 33.0 x 15.5 mm, 6 parts (4 on the bottom side), 23 nets.

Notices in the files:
parts and their libraries:
SparkFun-Retired: Licensing:Creative Commons ShareAlike 4.0 International - https://creativecommons.org/licenses/by-sa/4.0
